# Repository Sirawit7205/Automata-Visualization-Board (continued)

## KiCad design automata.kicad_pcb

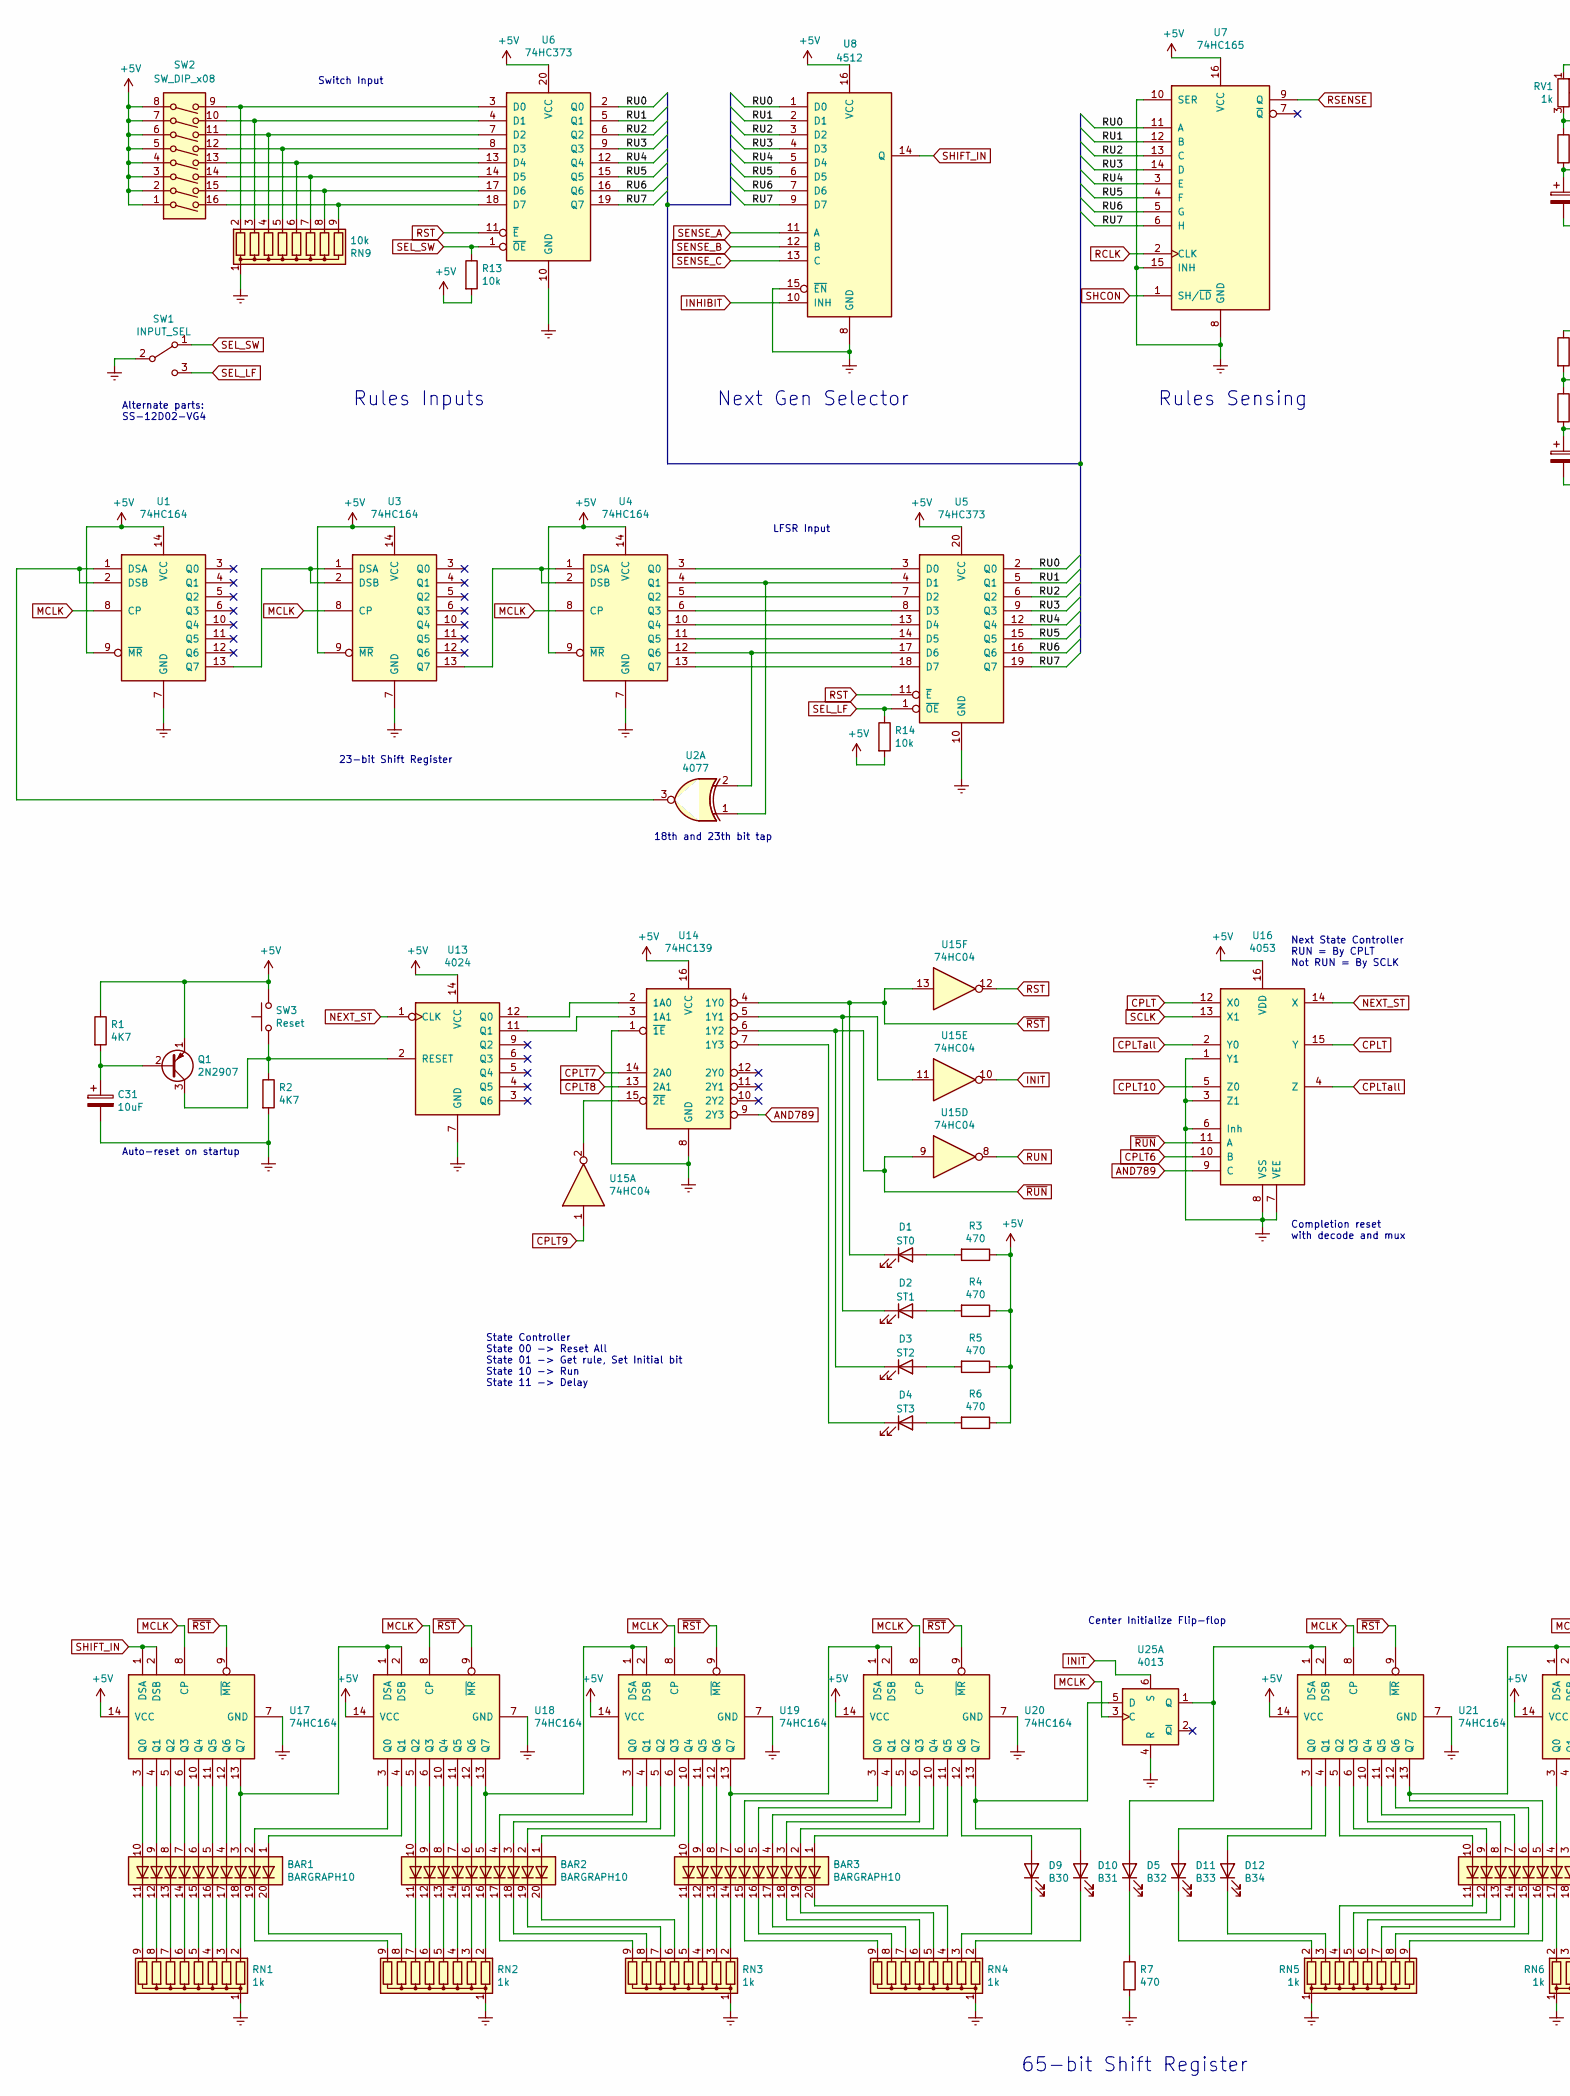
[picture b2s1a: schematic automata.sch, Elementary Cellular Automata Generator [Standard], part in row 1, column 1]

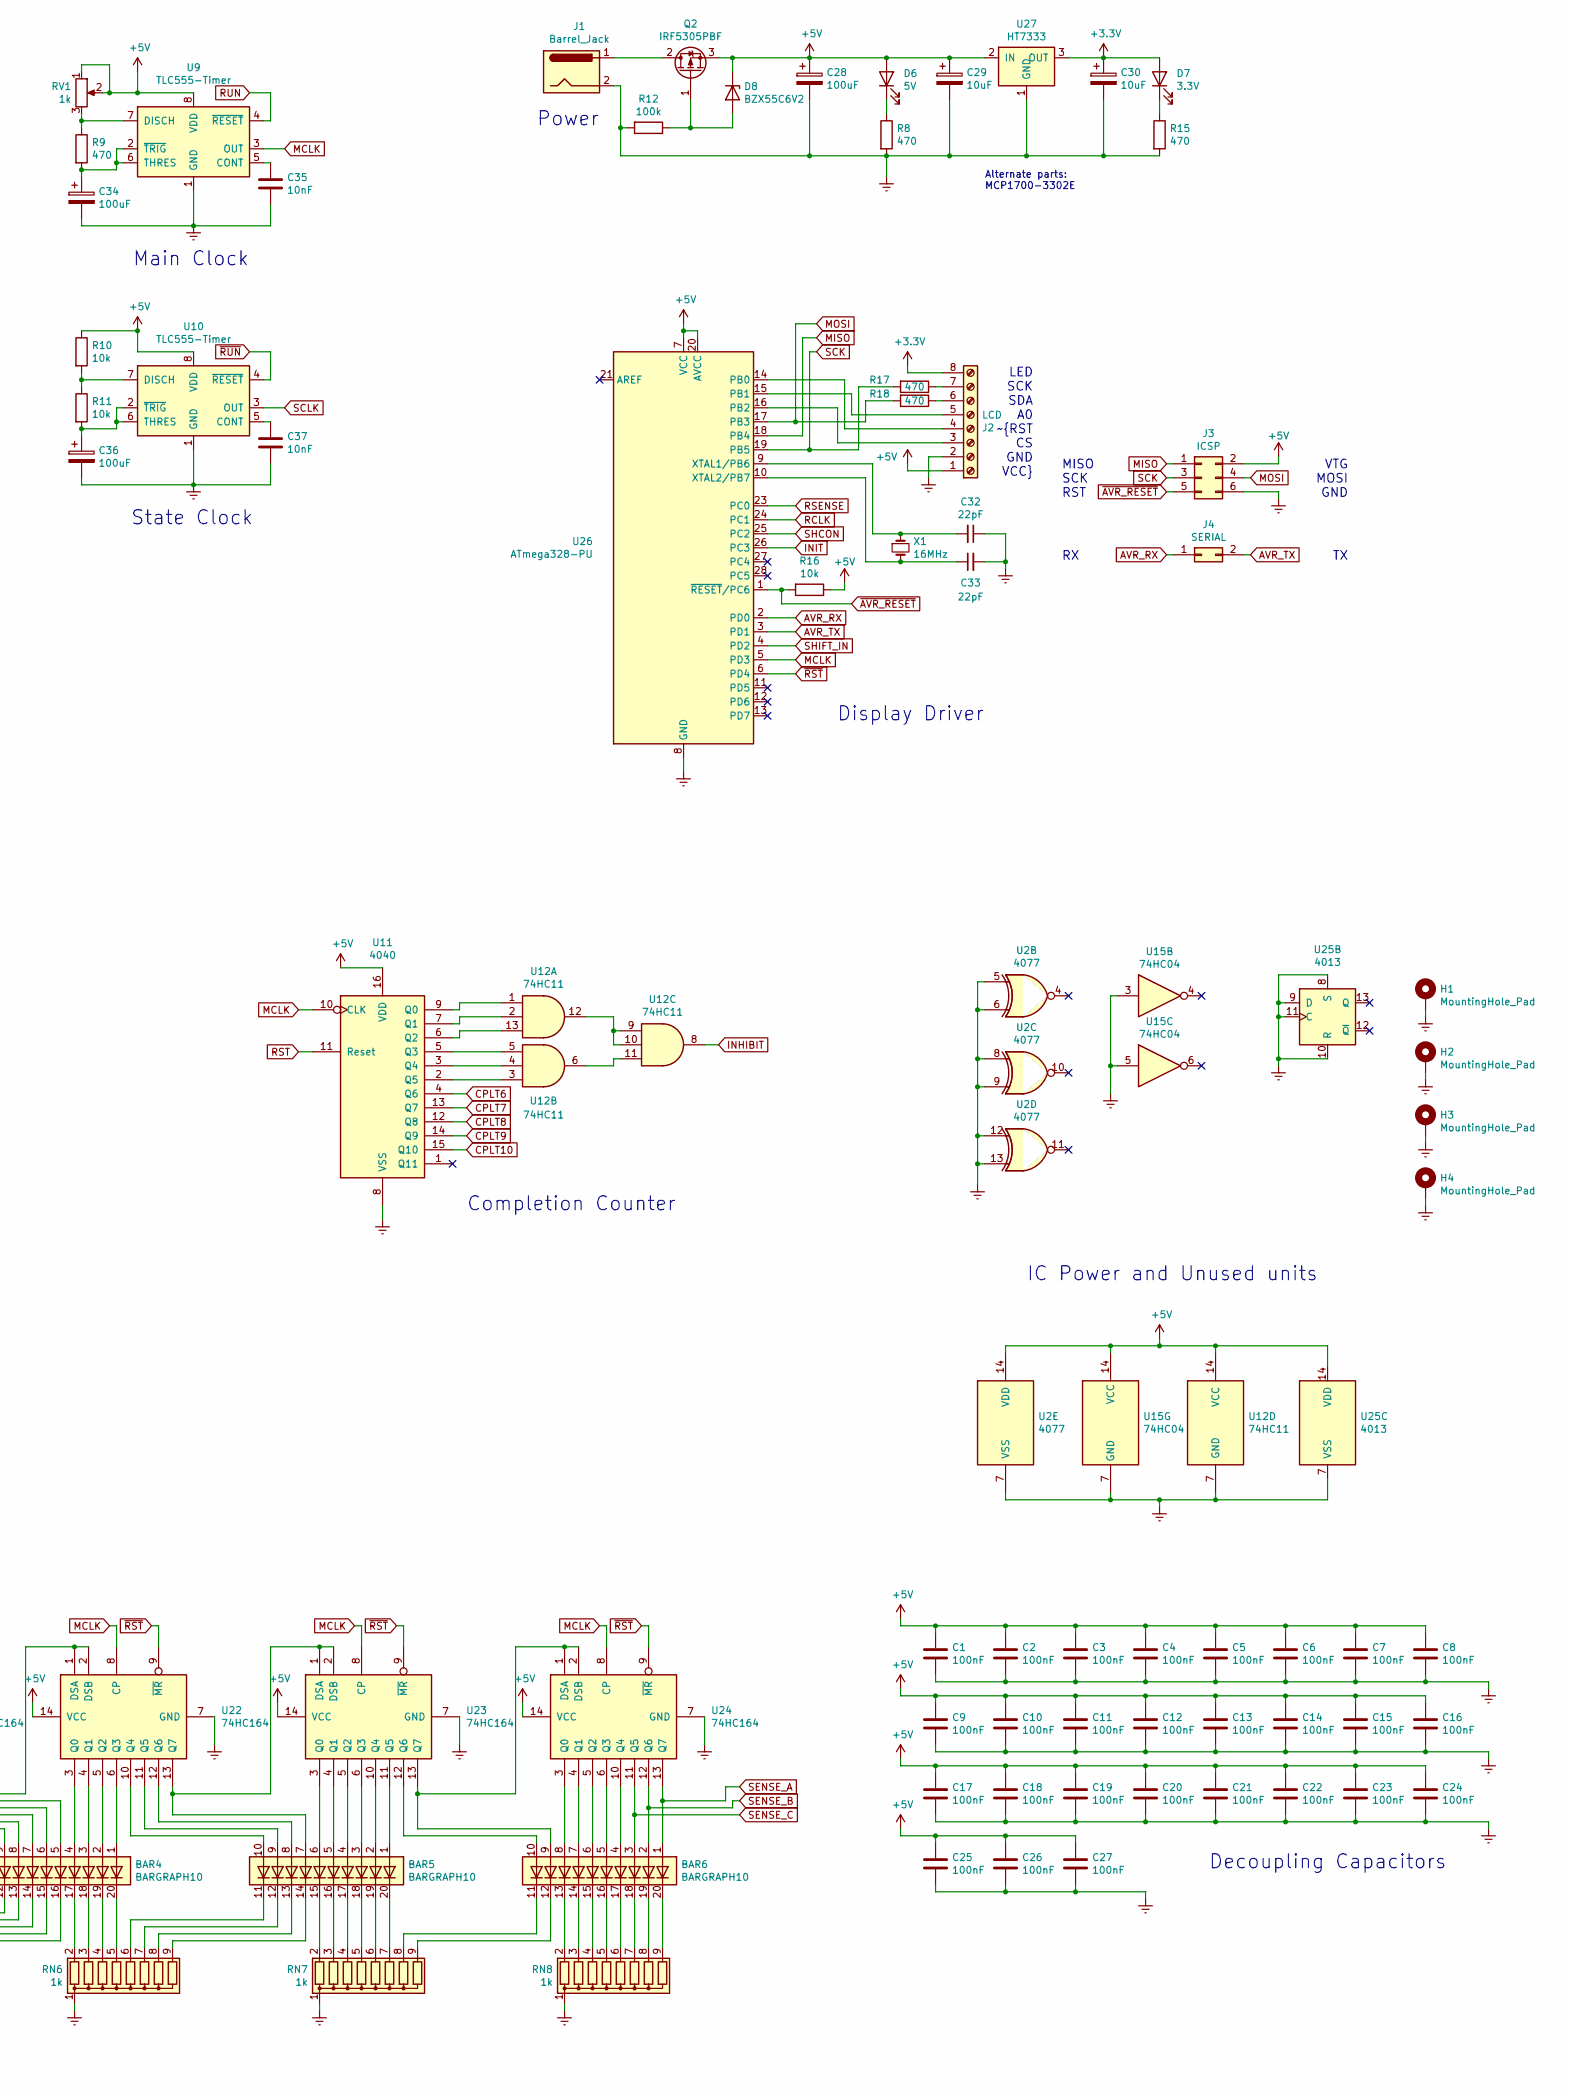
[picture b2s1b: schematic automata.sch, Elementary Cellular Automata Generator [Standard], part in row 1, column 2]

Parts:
BAR1, BAR2, BAR3, BAR4, BAR5, BAR6: BARGRAPH10; BARGRAPH_DIP_10
C1, C2, C3, C4, C5, C6, C7, C8, C9, C10, C11, C12, C13, C14, C15, C16, C17, C18, C19, C20, C21, C22, C23, C24, C25, C26, C27: 100nF; C_Disc_D5.1mm_W3.2mm_P5.00mm
C28, C34, C36: 100uF; CP_Radial_D8.0mm_P2.50mm
C29, C30, C31: 10uF; CP_Radial_D5.0mm_P2.00mm
C32, C33: 22pF; C_Disc_D5.1mm_W3.2mm_P5.00mm
C35, C37: 10nF; C_Disc_D5.1mm_W3.2mm_P5.00mm
D1: ST0; LED_Rectangular_W5.0mm_H2.0mm
D2: ST1; LED_Rectangular_W5.0mm_H2.0mm
D3: ST2; LED_Rectangular_W5.0mm_H2.0mm
D4: ST3; LED_Rectangular_W5.0mm_H2.0mm
D5: B32; LED_Rectangular_W5.0mm_H2.0mm
D6: 5V; LED_Rectangular_W5.0mm_H2.0mm
D7: 3.3V; LED_Rectangular_W5.0mm_H2.0mm
D8: BZX55C6V2; D_DO-35_SOD27_P7.62mm_Horizontal
D9: B30; LED_Rectangular_W5.0mm_H2.0mm
D10: B31; LED_Rectangular_W5.0mm_H2.0mm
D11: B33; LED_Rectangular_W5.0mm_H2.0mm
D12: B34; LED_Rectangular_W5.0mm_H2.0mm
H1, H2, H3, H4: MountingHole_Pad; MountingHole_2.2mm_M2_Pad
J1: Barrel_Jack; BarrelJack_Horizontal
J2: LCD; PinHeader_1x08_P2.54mm_Vertical
J3: ICSP; PinHeader_2x03_P2.54mm_Vertical
J4: SERIAL; PinHeader_2x01_P2.54mm_Vertical
Q1: 2N2907; TO-92_Inline
Q2: IRF5305PBF; TO-220-3_Horizontal_TabDown
R1, R2: 4K7; R_Axial_DIN0204_L3.6mm_D1.6mm_P7.62mm_Horizontal
R3, R4, R5, R6, R7, R9, R17, R18: 470; R_Axial_DIN0204_L3.6mm_D1.6mm_P2.54mm_Vertical
R8, R15: 470; R_Axial_DIN0204_L3.6mm_D1.6mm_P7.62mm_Horizontal
R10, R11: 10k; R_Axial_DIN0204_L3.6mm_D1.6mm_P2.54mm_Vertical
R12: 100k; R_Axial_DIN0204_L3.6mm_D1.6mm_P7.62mm_Horizontal
R13, R14, R16: 10k; R_Axial_DIN0204_L3.6mm_D1.6mm_P7.62mm_Horizontal
RN1, RN2, RN3, RN4, RN5, RN6, RN7, RN8: 1k; R_Array_SIP9
RN9: 10k; R_Array_SIP9
RV1: 1k; 3362P_1
SW1: INPUT_SEL; OS102011MA1QN1
SW2: SW_DIP_x08; SW_DIP_SPSTx08_Slide_9.78x22.5mm_W7.62mm_P2.54mm
SW3: Reset; SW_PUSH_6mm
U1, U3, U4, U17, U18, U19, U20, U21, U22, U23, U24: 74HC164; DIP-14_W7.62mm_Socket
U2: 4077; DIP-14_W7.62mm_Socket
U5, U6: 74HC373; DIP-20_W7.62mm_Socket
U7: 74HC165; DIP-16_W7.62mm_Socket
U8: 4512; DIP-16_W7.62mm_Socket
U9, U10: TLC555-Timer; DIP-8_W7.62mm_Socket
U11: 4040; DIP-16_W7.62mm_Socket
U12: 74HC11; DIP-14_W7.62mm_Socket
U13: 4024; DIP-14_W7.62mm_Socket
U14: 74HC139; DIP-16_W7.62mm_Socket
U15: 74HC04; DIP-14_W7.62mm_Socket
U16: 4053; DIP-16_W7.62mm_Socket
U25: 4013; DIP-14_W7.62mm_Socket
U26: ATmega328-PU; DIP-28_W7.62mm_Socket
U27: HT7333; TO-92_Inline
X1: 16MHz; Crystal_HC49-4H_Vertical

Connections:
+3V3: C30.1, D7.2 (A), J2.8, U27.3 (OUT)
+5V: C1.1, C2.1, C3.1, C4.1, C5.1, C6.1, C7.1, C8.1, C9.1, C10.1, C11.1, C12.1, C13.1, C14.1, C15.1, C16.1, C17.1, C18.1, C19.1, C20.1, C21.1, C22.1, C23.1, C24.1, C25.1, C26.1, C27.1, C28.1, C29.1, D6.2 (A), D8.1 (K), J2.1, J3.2, Q1.1 (E), Q2.3 (S), R1.1, R3.1, R4.1, R5.1, R6.1, R10.1, R13.2, R14.2, R16.1, RV1.1, RV1.2, SW2.1, SW2.2, SW2.3, SW2.4, SW2.5, SW2.6, SW2.7, SW2.8, SW3.2, U1.9 (~MR), U1.14 (VCC), U2.14 (VDD), U3.9 (~MR), U3.14 (VCC), U4.9 (~MR), U4.14 (VCC), U5.20 (VCC), U6.20 (VCC), U7.16 (VCC), U8.16 (VCC), U9.8 (VDD), U10.8 (VDD), U11.16 (VDD), U12.14 (VCC), U13.14 (VCC), U14.16 (VCC), U15.14 (VCC), U16.16 (VDD), U17.14 (VCC), U18.14 (VCC), U19.14 (VCC), U20.14 (VCC), U21.14 (VCC), U22.14 (VCC), U23.14 (VCC), U24.14 (VCC), U25.14 (VDD), U26.7 (VCC), U26.20 (AVCC), U27.2 (IN)
/RU0: U5.2 (Q0), U6.2 (Q0), U7.11 (A), U8.1 (D0)
/RU1: U5.5 (Q1), U6.5 (Q1), U7.12 (B), U8.2 (D1)
/RU2: U5.6 (Q2), U6.6 (Q2), U7.13 (C), U8.3 (D2)
/RU3: U5.9 (Q3), U6.9 (Q3), U7.14 (D), U8.4 (D3)
/RU4: U5.12 (Q4), U6.12 (Q4), U7.3 (E), U8.5 (D4)
/RU5: U5.15 (Q5), U6.15 (Q5), U7.4 (F), U8.6 (D5)
/RU6: U5.16 (Q6), U6.16 (Q6), U7.5 (G), U8.7 (D6)
/RU7: U5.19 (Q7), U6.19 (Q7), U7.6 (H), U8.9 (D7)
AND789: U14.9 (2Y3), U16.9 (C)
AVR_RX: J4.1, U26.2 (PD0)
AVR_TX: J4.2, U26.3 (PD1)
CPLT: U16.12 (X0), U16.15 (Y)
CPLT6: U11.4 (Q6), U16.10 (B)
CPLT7: U11.13 (Q7), U14.14 (2A0)
CPLT8: U11.12 (Q8), U14.13 (2A1)
CPLT9: U11.14 (Q9), U15.1
CPLT10: U11.15 (Q10), U16.5 (Z0)
CPLTall: U16.2 (Y0), U16.4 (Z)
GNDREF: C1.2, C2.2, C3.2, C4.2, C5.2, C6.2, C7.2, C8.2, C9.2, C10.2, C11.2, C12.2, C13.2, C14.2, C15.2, C16.2, C17.2, C18.2, C19.2, C20.2, C21.2, C22.2, C23.2, C24.2, C25.2, C26.2, C27.2, C28.2, C29.2, C30.2, C31.2, C32.1, C33.2, C34.2, C35.2, C36.2, C37.2, H1.1, H2.1, H3.1, H4.1, J1.2, J2.2, J3.6, R2.2, R7.2, R8.2, R12.2, R15.2, RN1.1 (common), RN2.1 (common), RN3.1 (common), RN4.1 (common), RN5.1 (common), RN6.1 (common), RN7.1 (common), RN8.1 (common), RN9.1 (common), SW1.2 (B), U1.7 (GND), U2.5, U2.6, U2.7 (VSS), U2.8, U2.9, U2.12, U2.13, U3.7 (GND), U4.7 (GND), U5.10 (GND), U6.10 (GND), U7.8 (GND), U7.10 (SER), U7.15 (INH), U8.8 (GND), U8.15 (~EN), U9.1 (GND), U10.1 (GND), U11.8 (VSS), U12.7 (GND), U13.7 (GND), U14.1 (~1E), U14.8 (GND), U15.3, U15.5, U15.7 (GND), U16.1 (Y1), U16.3 (Z1), U16.6 (Inh), U16.7 (VEE), U16.8 (VSS), U17.7 (GND), U18.7 (GND), U19.7 (GND), U20.7 (GND), U21.7 (GND), U22.7 (GND), U23.7 (GND), U24.7 (GND), U25.4 (R), U25.7 (VSS), U25.8 (S), U25.9 (D), U25.10 (R), U25.11 (C), U26.8 (GND), U26.22 (GND), U27.1 (GND)
INHIBIT: U8.10 (INH), U12.8
INIT: U15.10, U25.6 (S), U26.26 (PC3)
MCLK: U1.8 (CP), U3.8 (CP), U4.8 (CP), U9.3 (OUT), U11.10 (CLK), U17.8 (CP), U18.8 (CP), U19.8 (CP), U20.8 (CP), U21.8 (CP), U22.8 (CP), U23.8 (CP), U24.8 (CP), U25.3 (C), U26.5 (PD3)
MISO: J3.1, U26.18 (PB4)
MOSI: J3.4, R18.2, U26.17 (PB3)
NEXT_ST: U13.1 (CLK), U16.14 (X)
unnamed: BAR1.1 (A), U18.4 (Q1)
unnamed: BAR1.2 (A), U18.3 (Q0)
unnamed: BAR1.3 (A), U17.13 (Q7), U18.1 (DSA), U18.2 (DSB)
unnamed: BAR1.4 (A), U17.12 (Q6)
unnamed: BAR1.5 (A), U17.11 (Q5)
unnamed: BAR1.6 (A), U17.10 (Q4)
unnamed: BAR1.7 (A), U17.6 (Q3)
unnamed: BAR1.8 (A), U17.5 (Q2)
unnamed: BAR1.9 (A), U17.4 (Q1)
unnamed: BAR1.10 (A), U17.3 (Q0)
unnamed: BAR1.11 (K), RN1.9 (R8)
unnamed: BAR1.12 (K), RN1.8 (R7)
unnamed: BAR1.13 (K), RN1.7 (R6)
unnamed: BAR1.14 (K), RN1.6 (R5)
unnamed: BAR1.15 (K), RN1.5 (R4)
unnamed: BAR1.16 (K), RN1.4 (R3)
unnamed: BAR1.17 (K), RN1.3 (R2)
unnamed: BAR1.18 (K), RN1.2 (R1)
unnamed: BAR1.19 (K), RN2.9 (R8)
unnamed: BAR1.20 (K), RN2.8 (R7)
unnamed: BAR2.1 (A), U19.6 (Q3)
unnamed: BAR2.2 (A), U19.5 (Q2)
unnamed: BAR2.3 (A), U19.4 (Q1)
unnamed: BAR2.4 (A), U19.3 (Q0)
unnamed: BAR2.5 (A), U18.13 (Q7), U19.1 (DSA), U19.2 (DSB)
unnamed: BAR2.6 (A), U18.12 (Q6)
unnamed: BAR2.7 (A), U18.11 (Q5)
unnamed: BAR2.8 (A), U18.10 (Q4)
unnamed: BAR2.9 (A), U18.6 (Q3)
unnamed: BAR2.10 (A), U18.5 (Q2)
unnamed: BAR2.11 (K), RN2.7 (R6)
unnamed: BAR2.12 (K), RN2.6 (R5)
unnamed: BAR2.13 (K), RN2.5 (R4)
unnamed: BAR2.14 (K), RN2.4 (R3)
unnamed: BAR2.15 (K), RN2.3 (R2)
unnamed: BAR2.16 (K), RN2.2 (R1)
unnamed: BAR2.17 (K), RN3.9 (R8)
unnamed: BAR2.18 (K), RN3.8 (R7)
unnamed: BAR2.19 (K), RN3.7 (R6)
unnamed: BAR2.20 (K), RN3.6 (R5)
unnamed: BAR3.1 (A), U20.11 (Q5)
unnamed: BAR3.2 (A), U20.10 (Q4)
unnamed: BAR3.3 (A), U20.6 (Q3)
unnamed: BAR3.4 (A), U20.5 (Q2)
unnamed: BAR3.5 (A), U20.4 (Q1)
unnamed: BAR3.6 (A), U20.3 (Q0)
unnamed: BAR3.7 (A), U19.13 (Q7), U20.1 (DSA), U20.2 (DSB)
unnamed: BAR3.8 (A), U19.12 (Q6)
unnamed: BAR3.9 (A), U19.11 (Q5)
unnamed: BAR3.10 (A), U19.10 (Q4)
unnamed: BAR3.11 (K), RN3.5 (R4)
unnamed: BAR3.12 (K), RN3.4 (R3)
unnamed: BAR3.13 (K), RN3.3 (R2)
unnamed: BAR3.14 (K), RN3.2 (R1)
unnamed: BAR3.15 (K), RN4.9 (R8)
unnamed: BAR3.16 (K), RN4.8 (R7)
unnamed: BAR3.17 (K), RN4.7 (R6)
unnamed: BAR3.18 (K), RN4.6 (R5)
unnamed: BAR3.19 (K), RN4.5 (R4)
unnamed: BAR3.20 (K), RN4.4 (R3)
unnamed: BAR4.1 (A), U22.6 (Q3)
unnamed: BAR4.2 (A), U22.5 (Q2)
unnamed: BAR4.3 (A), U22.4 (Q1)
unnamed: BAR4.4 (A), U22.3 (Q0)
unnamed: BAR4.5 (A), U21.13 (Q7), U22.1 (DSA), U22.2 (DSB)
unnamed: BAR4.6 (A), U21.12 (Q6)
unnamed: BAR4.7 (A), U21.11 (Q5)
unnamed: BAR4.8 (A), U21.10 (Q4)
unnamed: BAR4.9 (A), U21.6 (Q3)
unnamed: BAR4.10 (A), U21.5 (Q2)
unnamed: BAR4.11 (K), RN5.4 (R3)
unnamed: BAR4.12 (K), RN5.5 (R4)
unnamed: BAR4.13 (K), RN5.6 (R5)
unnamed: BAR4.14 (K), RN5.7 (R6)
unnamed: BAR4.15 (K), RN5.8 (R7)
unnamed: BAR4.16 (K), RN5.9 (R8)
unnamed: BAR4.17 (K), RN6.2 (R1)
unnamed: BAR4.18 (K), RN6.3 (R2)
unnamed: BAR4.19 (K), RN6.4 (R3)
unnamed: BAR4.20 (K), RN6.5 (R4)
unnamed: BAR5.1 (A), U23.11 (Q5)
unnamed: BAR5.2 (A), U23.10 (Q4)
unnamed: BAR5.3 (A), U23.6 (Q3)
unnamed: BAR5.4 (A), U23.5 (Q2)
unnamed: BAR5.5 (A), U23.4 (Q1)
unnamed: BAR5.6 (A), U23.3 (Q0)
unnamed: BAR5.7 (A), U22.13 (Q7), U23.1 (DSA), U23.2 (DSB)
unnamed: BAR5.8 (A), U22.12 (Q6)
unnamed: BAR5.9 (A), U22.11 (Q5)
unnamed: BAR5.10 (A), U22.10 (Q4)
unnamed: BAR5.11 (K), RN6.6 (R5)
unnamed: BAR5.12 (K), RN6.7 (R6)
unnamed: BAR5.13 (K), RN6.8 (R7)
unnamed: BAR5.14 (K), RN6.9 (R8)
unnamed: BAR5.15 (K), RN7.2 (R1)
unnamed: BAR5.16 (K), RN7.3 (R2)
unnamed: BAR5.17 (K), RN7.4 (R3)
unnamed: BAR5.18 (K), RN7.5 (R4)
unnamed: BAR5.19 (K), RN7.6 (R5)
unnamed: BAR5.20 (K), RN7.7 (R6)
unnamed: BAR6.4 (A), U24.10 (Q4)
unnamed: BAR6.5 (A), U24.6 (Q3)
unnamed: BAR6.6 (A), U24.5 (Q2)
unnamed: BAR6.7 (A), U24.4 (Q1)
unnamed: BAR6.8 (A), U24.3 (Q0)
unnamed: BAR6.9 (A), U23.13 (Q7), U24.1 (DSA), U24.2 (DSB)
unnamed: BAR6.10 (A), U23.12 (Q6)
unnamed: BAR6.11 (K), RN7.8 (R7)
unnamed: BAR6.12 (K), RN7.9 (R8)
unnamed: BAR6.13 (K), RN8.2 (R1)
unnamed: BAR6.14 (K), RN8.3 (R2)
unnamed: BAR6.15 (K), RN8.4 (R3)
unnamed: BAR6.16 (K), RN8.5 (R4)
unnamed: BAR6.17 (K), RN8.6 (R5)
unnamed: BAR6.18 (K), RN8.7 (R6)
unnamed: BAR6.19 (K), RN8.8 (R7)
unnamed: BAR6.20 (K), RN8.9 (R8)
unnamed: C31.1, Q1.2 (B), R1.2
unnamed: C32.2, U26.9 (XTAL1/PB6), X1.1
unnamed: C33.1, U26.10 (XTAL2/PB7), X1.2
unnamed: C34.1, R9.2, U9.2 (~TRIG), U9.6 (THRES)
unnamed: C35.1, U9.5 (CONT)
unnamed: C36.1, R11.2, U10.2 (~TRIG), U10.6 (THRES)
unnamed: C37.1, U10.5 (CONT)
unnamed: D1.2 (A), R3.2
unnamed: D2.1 (K), U14.5 (1Y1), U15.11
unnamed: D2.2 (A), R4.2
unnamed: D3.2 (A), R5.2
unnamed: D4.1 (K), U14.7 (1Y3)
unnamed: D4.2 (A), R6.2
unnamed: D5.1 (K), R7.1
unnamed: D5.2 (A), U21.1 (DSA), U21.2 (DSB), U25.1 (Q)
unnamed: D6.1 (K), R8.1
unnamed: D7.1 (K), R15.1
unnamed: D8.2 (A), Q2.1 (G), R12.1
unnamed: D9.1 (K), RN4.3 (R2)
unnamed: D9.2 (A), U20.12 (Q6)
unnamed: D10.1 (K), RN4.2 (R1)
unnamed: D10.2 (A), U20.13 (Q7), U25.5 (D)
unnamed: D11.1 (K), RN5.2 (R1)
unnamed: D11.2 (A), U21.3 (Q0)
unnamed: D12.1 (K), RN5.3 (R2)
unnamed: D12.2 (A), U21.4 (Q1)
unnamed: J1.1, Q2.2 (D)
unnamed: J2.3, U26.16 (PB2)
unnamed: J2.4, U26.14 (PB0)
unnamed: J2.5, U26.15 (PB1)
unnamed: J2.6, R18.1
unnamed: J2.7, R17.1
unnamed: Q1.3 (C), R2.1, SW3.1, U13.2 (RESET)
unnamed: R9.1, RV1.3, U9.7 (DISCH)
unnamed: R10.2, R11.1, U10.7 (DISCH)
unnamed: RN9.2 (R1), SW2.9, U6.3 (D0)
unnamed: RN9.3 (R2), SW2.10, U6.4 (D1)
unnamed: RN9.4 (R3), SW2.11, U6.7 (D2)
unnamed: RN9.5 (R4), SW2.12, U6.8 (D3)
unnamed: RN9.6 (R5), SW2.13, U6.13 (D4)
unnamed: RN9.7 (R6), SW2.14, U6.14 (D5)
unnamed: RN9.8 (R7), SW2.15, U6.17 (D6)
unnamed: RN9.9 (R8), SW2.16, U6.18 (D7)
unnamed: U1.1 (DSA), U1.2 (DSB), U2.3
unnamed: U1.13 (Q7), U3.1 (DSA), U3.2 (DSB)
unnamed: U2.1, U4.4 (Q1), U5.4 (D1)
unnamed: U2.2, U4.12 (Q6), U5.17 (D6)
unnamed: U3.13 (Q7), U4.1 (DSA), U4.2 (DSB)
unnamed: U4.3 (Q0), U5.3 (D0)
unnamed: U4.5 (Q2), U5.7 (D2)
unnamed: U4.6 (Q3), U5.8 (D3)
unnamed: U4.10 (Q4), U5.13 (D4)
unnamed: U4.11 (Q5), U5.14 (D5)
unnamed: U4.13 (Q7), U5.18 (D7)
unnamed: U11.2 (Q5), U12.3
unnamed: U11.3 (Q4), U12.4
unnamed: U11.5 (Q3), U12.5
unnamed: U11.6 (Q2), U12.13
unnamed: U11.7 (Q1), U12.2
unnamed: U11.9 (Q0), U12.1
unnamed: U12.9, U12.10, U12.12
unnamed: U12.6, U12.11
unnamed: U13.11 (Q1), U14.3 (1A1)
unnamed: U13.12 (Q0), U14.2 (1A0)
unnamed: U14.15 (~2E), U15.2
RCLK: U7.2 (CLK), U26.24 (PC1)
RSENSE: U7.9 (Q), U26.23 (PC0)
RST: U5.11 (~E), U6.11 (~E), U11.11 (Reset), U15.12
RUN: U9.4 (~RESET), U15.8
SCK: J3.3, R17.2, U26.19 (PB5)
SCLK: U10.3 (OUT), U16.13 (X1)
SEL_LF: R14.1, SW1.3 (C), U5.1 (~OE)
SEL_SW: R13.1, SW1.1 (A), U6.1 (~OE)
SENSE_A: BAR6.1 (A), U8.11 (A), U24.13 (Q7)
SENSE_B: BAR6.2 (A), U8.12 (B), U24.12 (Q6)
SENSE_C: BAR6.3 (A), U8.13 (C), U24.11 (Q5)
SHCON: U7.1 (SH/~LD), U26.25 (PC2)
SHIFT_IN: U8.14 (Q), U17.1 (DSA), U17.2 (DSB), U26.4 (PD2)
~AVR_RESET: J3.5, R16.2, U26.1 (~RESET~/PC6)
~RST: D1.1 (K), U14.4 (1Y0), U15.13, U17.9 (~MR), U18.9 (~MR), U19.9 (~MR), U20.9 (~MR), U21.9 (~MR), U22.9 (~MR), U23.9 (~MR), U24.9 (~MR), U26.6 (PD4)
~RUN: D3.1 (K), U10.4 (~RESET), U14.6 (1Y2), U15.9, U16.11 (A)

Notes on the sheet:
Switch Input
Rules Inputs
Next Gen Selector
Completion Counter
LED SCK SDA A0 ~RST CS GND VCC
Power
Display Driver
Rules Sensing
State Controller State 00 -> Reset All State 01 -> Get rule, Set Initial bit State 10 -> Run State 11 -> Delay
Auto-reset on startup
State Clock
Next State Controller RUN = By CPLT Not RUN = By SCLK
65-bit Shift Register
Center Initialize Flip-flop
Completion reset with decode and mux
Main Clock
Decoupling Capacitors
IC Power and Unused units
VTG MOSI GND
MISO SCK RST
23-bit Shift Register
18th and 23th bit tap
LFSR Input
Alternate parts: MCP1700-3302E
Alternate parts: SS-12D02-VG4

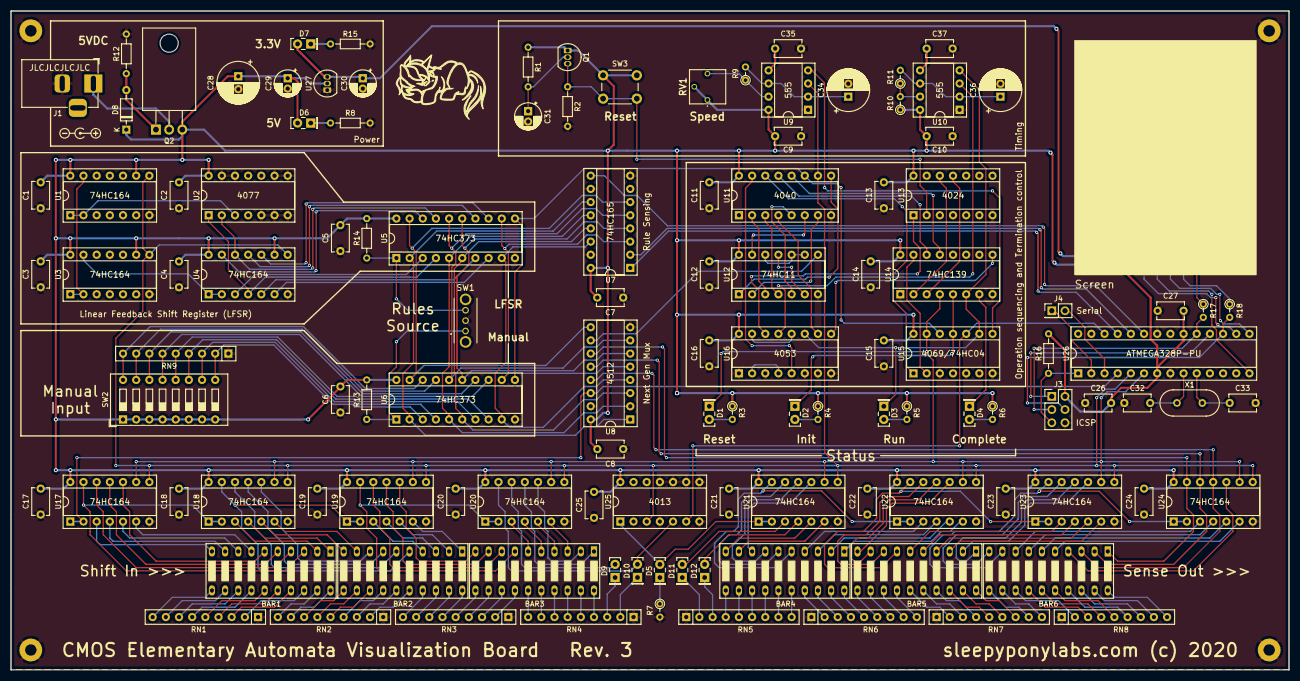
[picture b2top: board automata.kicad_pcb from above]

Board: 2 copper layers, 246.4 x 127.0 mm, 126 parts (0 on the bottom side), 225 nets.

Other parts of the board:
G1: LOGO; sleepylogo_20mm
REF1: Symbol_Barrel_Polarity

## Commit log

2020-05-16 revision 2
2020-05-16 Credits
2020-05-19 Add pin 1 indicators to some parts in pcb (temporary)
2020-07-16 Remove rescue libs and fixed MC14557 symbol error
2020-07-18 Modified display driver code
2020-07-18 Rev 3 design update for SMD version
2020-07-19 Rev 3 design update for standard version
2020-08-26 Changed LED bargraphs to 10-bar variant
2020-08-26 Document update
2020-09-12 LDO change to streamline the inventory
2020-10-03 reroute standard pcb
2020-12-02 PCB reroute
2020-12-29 Silkscreen update
2021-01-03 Remove old disclaimer from README
